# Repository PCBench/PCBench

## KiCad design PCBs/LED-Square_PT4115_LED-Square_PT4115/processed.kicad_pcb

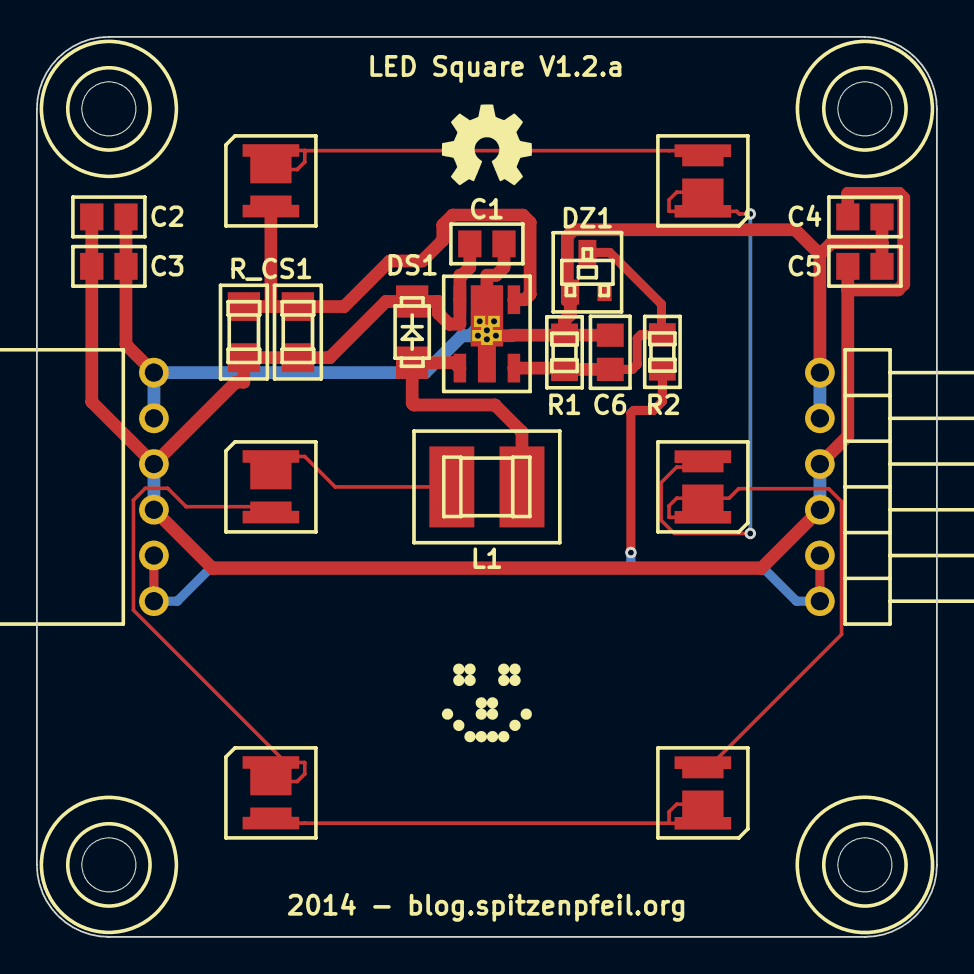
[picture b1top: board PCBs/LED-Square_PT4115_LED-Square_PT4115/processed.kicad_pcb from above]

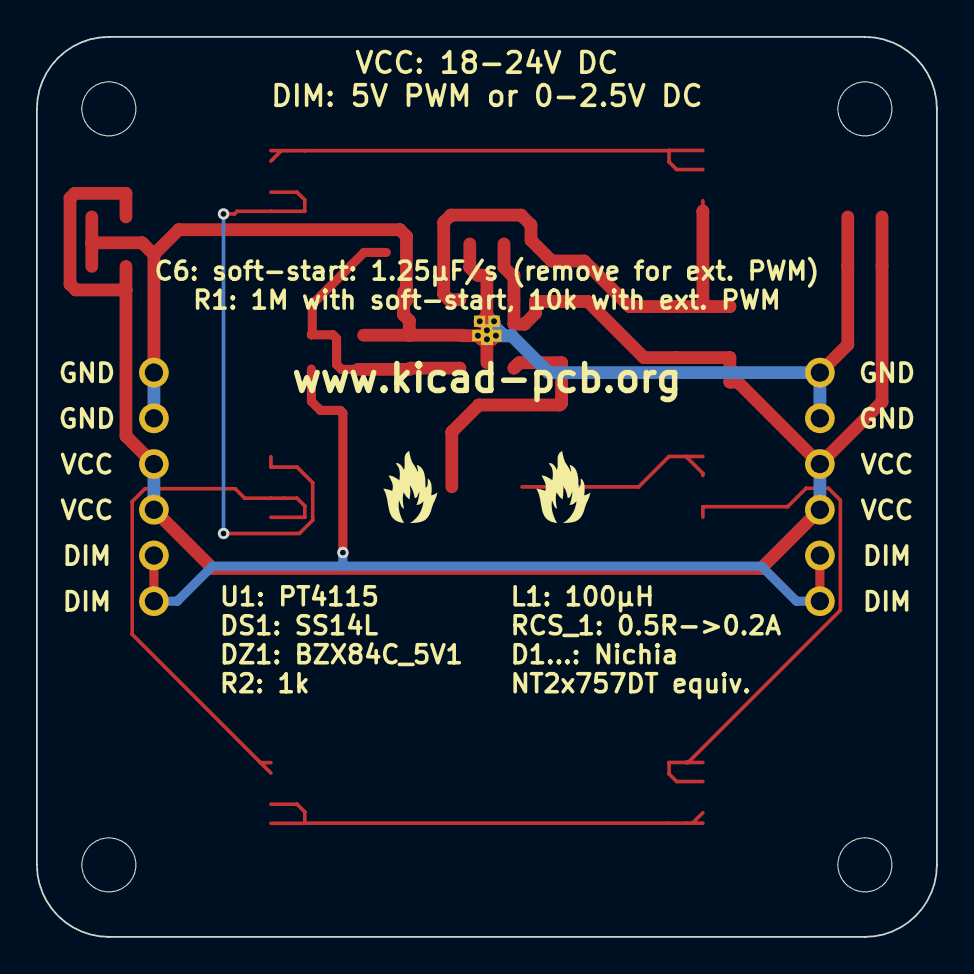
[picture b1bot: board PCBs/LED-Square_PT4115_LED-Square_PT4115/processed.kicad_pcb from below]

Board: 2 copper layers, 50.0 x 50.0 mm, 30 parts (2 on the bottom side), 12 nets.

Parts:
C1, C2, C3, C4, C5: 10µF; MADW__C0805
C6: 1.25µF/s; MADW__C0805
D1, D2, D3, D4, D5, D6: LED; MADW__Nichia-NT2x757DT
DS1: SS14L (40V, 1A); MADW__diode_sub-SMA
DZ1: BZX84C_5V1; MADW__SOT23
G1: OSHW-logo_silkscreen_5mm
G2: LED_smile_silkscreen_5mm
G3, G4: fire_silkscreen-back_4mm
L1: 100µH; MADW__L4.8x3.3mm
MH1, MH2, MH3, MH4: CONN_1; MADW__mounting_hole_3mm
P1: IN; MADW__edge-connector_SIL6_female
P2: OUT; MADW__edge-connector_SIL6_male
R1: 1M; MADW__R0805
R2: 1k; MADW__R0805
R_CS1, R_CS2: 1R1; MADW__R1206
U1: PT4115-SOT89-5; MADW__SOT89-5

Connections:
/CSN: D1.1, R_CS1.2, R_CS2.2, U1.4
/D1HS: D1.2, D2.1
/D2HS: D2.2, D3.1
/D3HS: D3.2, D4.1
/D4HS: D4.2, D5.1
/D5HS: D5.2, D6.1
/D6HS: D6.2, L1.2
/DIM: P1.5, P1.6, P2.1, P2.2, R2.1
/SW: DS1.1, L1.1, U1.1
/_dim: C6.1, DZ1.3, R1.1, R2.2, U1.3
GND: C1.2, C2.2, C3.2, C4.2, C5.2, C6.2, DZ1.1, P1.1, P1.2, P2.5, P2.6, R1.2, U1.2
VCC: C1.1, C2.1, C3.1, C4.1, C5.1, DS1.2, P1.3, P1.4, P2.3, P2.4, R_CS1.1, R_CS2.1, U1.5

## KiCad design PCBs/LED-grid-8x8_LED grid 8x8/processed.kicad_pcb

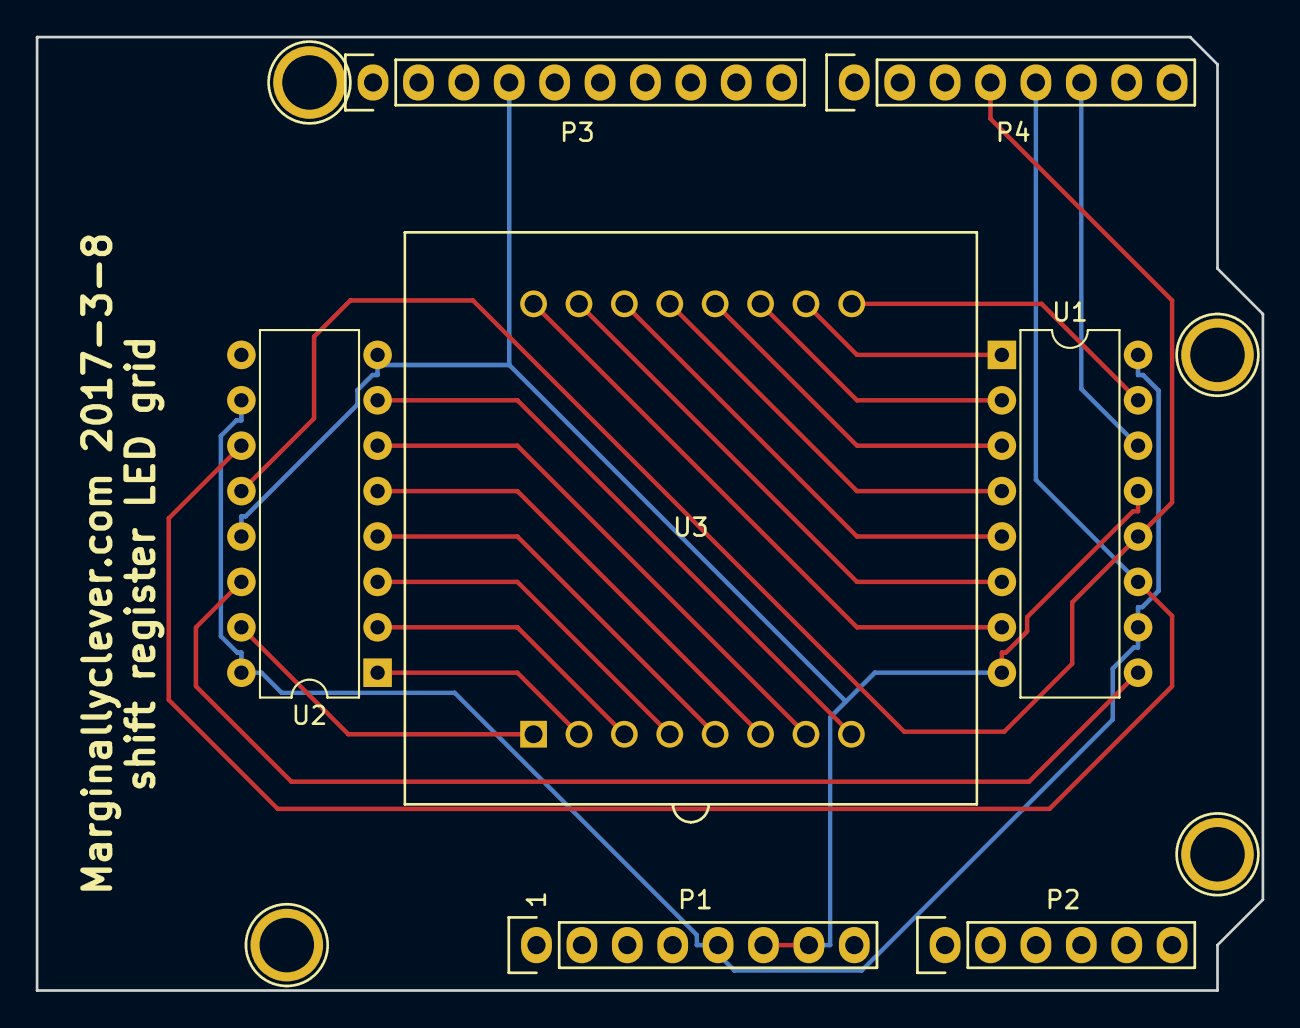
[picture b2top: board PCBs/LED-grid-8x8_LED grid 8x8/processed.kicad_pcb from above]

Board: 2 copper layers, 68.6 x 53.3 mm, 11 parts (0 on the bottom side), 22 nets.

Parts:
P1: Power; Socket_Strip_Arduino_1x08
P2: Analog; Socket_Strip_Arduino_1x06
P3: Digital; Socket_Strip_Arduino_1x10
P4: Digital; Socket_Strip_Arduino_1x08
P5, P6, P7, P8: CONN_1; Arduino_1pin
U1, U2: 74HC595; DIP-16_W7.62mm
U3: 1088BS

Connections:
+5V: P1.5, U1.10, U1.16, U2.10, U2.16
/2: P4.6, U1.14
/3(**): P4.5, U1.11, U2.11
/4: P4.4, U1.12, U2.12
GND: P1.6, P1.7, P3.4, U1.8, U1.13, U2.8, U2.13
unnamed: U1.1, U3.10
unnamed: U1.2, U3.11
unnamed: U1.3, U3.12
unnamed: U1.4, U3.13
unnamed: U1.5, U3.14
unnamed: U1.6, U3.15
unnamed: U1.7, U3.16
unnamed: U1.9, U2.14
unnamed: U1.15, U3.9
unnamed: U2.1, U3.2
unnamed: U2.2, U3.3
unnamed: U2.3, U3.4
unnamed: U2.4, U3.5
unnamed: U2.5, U3.6
unnamed: U2.6, U3.7
unnamed: U2.7, U3.8
unnamed: U2.15, U3.1

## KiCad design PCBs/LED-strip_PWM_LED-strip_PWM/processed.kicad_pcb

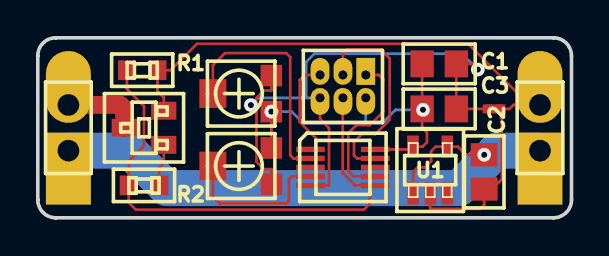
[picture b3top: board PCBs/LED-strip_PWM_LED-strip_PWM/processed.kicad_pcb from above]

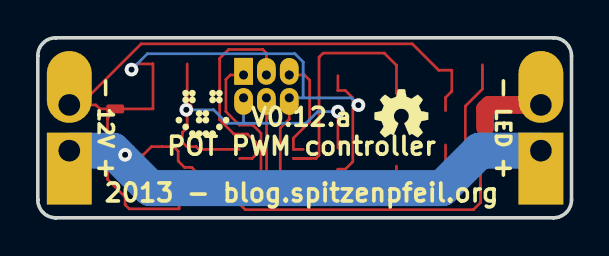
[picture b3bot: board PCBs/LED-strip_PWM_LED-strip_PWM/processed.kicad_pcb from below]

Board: 2 copper layers, 29.7 x 10.0 mm, 16 parts (2 on the bottom side), 12 nets.

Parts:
C1, C2: 100nF; MADW__C0805
C3: 4.7µF; MADW__C0805
G1: OSHW-logo_silkscreen_3mm
G2: LED_smile_silkscreen_3mm
IC1: MADW__ATTINY13-MM; MADW__MLF10
JP1: ISP; MADW__PIN_ARRAY_3x2_1.27mm
NJ1: NET-JOIN; MADW__SMD-net-noin-0.5mm
P1, P2: CONN_2; MADW__SIL-2
R1: 100k; MADW__R0603_2
R2: 150R; MADW__R0603_2
RV1, RV2: 50k; MADW__TC33X-POT
T1: AO3400; MADW__SOT23
U1: MCP1804-SOT23-5; MADW__SOT23-5

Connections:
/MISO: IC1.7, JP1.1
/MOSI: IC1.6, JP1.4, R1.2, R2.1
/POT1: IC1.2, RV1.2
/POT2: IC1.4, RV2.2
/RESET: IC1.1, JP1.5
/SCK: IC1.9, JP1.3
/Vin: C2.1, P1.1, P2.1, U1.1, U1.4
/drain: P2.2, T1.3
GND: C1.2, C3.2, IC1.5, JP1.6, NJ1.1, RV1.3, RV2.1
GNDPWR: C2.2, NJ1.2, P1.2, R1.1, T1.2, U1.2
unnamed: R2.2, T1.1
VCC: C1.1, C3.1, IC1.10, JP1.2, RV1.1, RV2.3, U1.5

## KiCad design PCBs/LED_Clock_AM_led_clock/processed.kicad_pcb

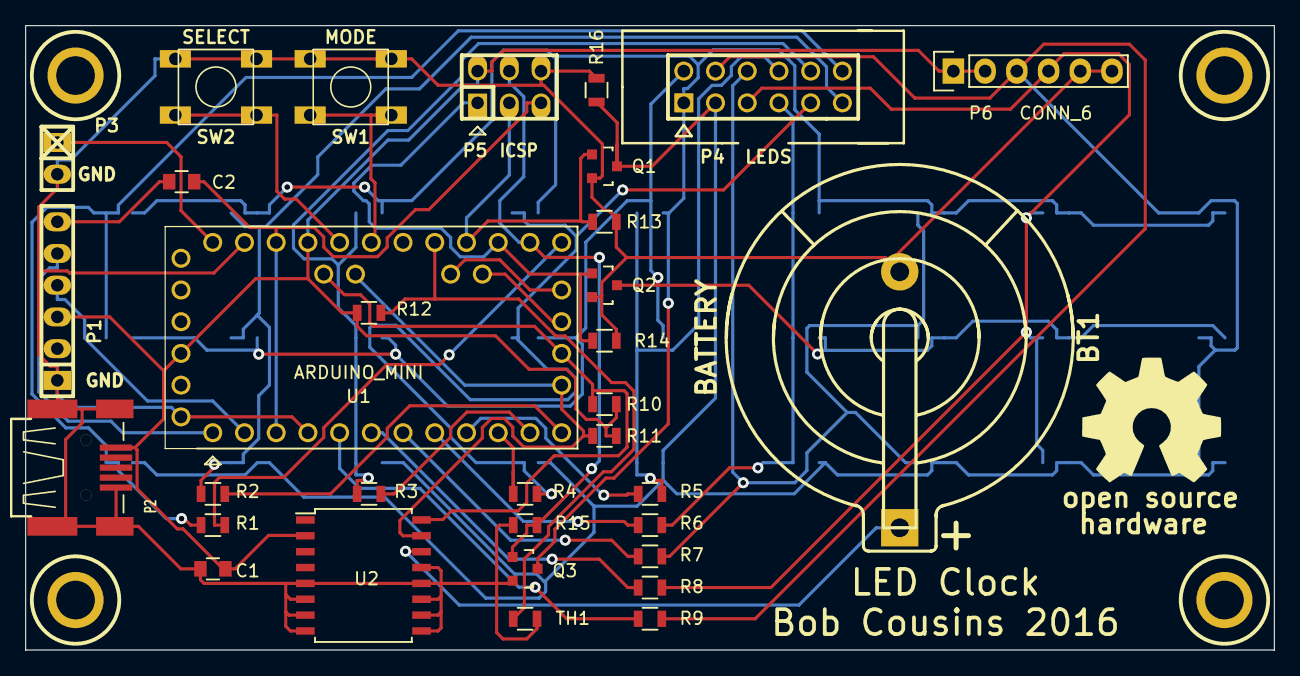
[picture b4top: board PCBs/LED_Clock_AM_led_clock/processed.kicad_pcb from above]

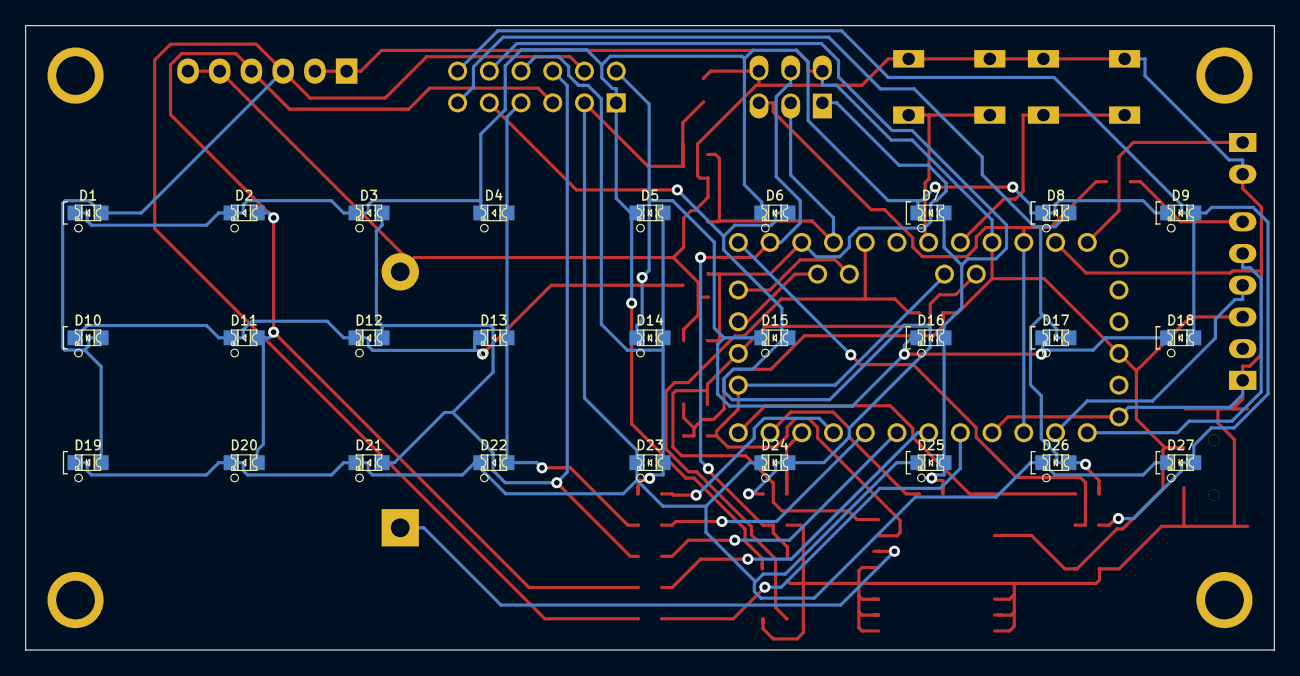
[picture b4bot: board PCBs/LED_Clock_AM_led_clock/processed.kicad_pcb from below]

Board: 2 copper layers, 100.0 x 50.0 mm, 65 parts (27 on the bottom side), 37 nets.

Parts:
BT1: BATTERY; keystone_106
C1, C2: 100nF; C_0805
D1, D7, D8, D9, D10, D16, D17, D18, D19, D25, D26, D27: LED; LED-0805_RED
D2, D3, D4, D11, D12, D13, D20, D21, D22: LED; LED-0805_GREEN
D5, D6, D14, D15, D23, D24: LED; LED-0805_BLUE
H1, H2, H3, H4: HOLE_RMC; HOLE_M3
M2: LOGO_OSHW; OSHW_logo_2
P1: SERIAL; pin_strip_6
P2: USBCONN; CONN_MiniAB_SMT_RMC
P3: 5-9V IN; pin_strip_2
P4: LEDS; PIN_ARRAY_6x2_RMC
P5: ICSP; pin_strip_3x2
P6: CONN_6; Pin_Header_Straight_1x06
Q1, Q2, Q3: BSS138; SOT-23
R1, R2, R3, R4, R5, R6, R7, R8, R9: 220; R_0805
R10, R11, R12: 4k7; R_0805
R13, R14, R15: 10k; R_0805
R16: 0R; R_0805
SW1: MODE; SW_6x6_MULTI
SW2: SELECT; SW_6x6_MULTI
TH1: 10k; R_0805
U1: ARDUINO_MINI
U2: DS3231N; SOIC-16_7.5x10.3mm_Pitch1.27mm

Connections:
+5V: C1.1, P1.3, P2.1, P5.2, P6.1, P6.2, R10.2, R11.2, R12.1, U1.+5V, U2.2
/MISO: P5.1, Q2.1, R14.1, U1.12
/MOSI: P5.4, Q3.1, R15.1, U1.11
/SCK: P5.3, Q1.1, R13.1, U1.13
/SCL: R10.1, U1.A5, U2.16
/SDA: R11.1, U1.A4, U2.15
/SW1: SW1.1, U1.A2
/SW2: SW2.1, U1.A3
/VIN: P3.1, U1.VIN
/~RST: C2.2, P5.5, U1.RST
COL1: D1.2, D10.2, D19.2, P4.4, P6.3, R9.2
COL2: D2.2, D11.2, D20.2, P4.5, P6.4, R8.2
COL3: D3.2, D12.2, D21.2, P4.6, R7.2
COL4: D4.2, D13.2, D22.2, P4.7, R6.2
COL5: D5.2, D14.2, D23.2, P4.8, R5.2
COL6: D6.2, D15.2, D24.2, P4.9, R4.2
COL7: D7.2, D16.2, D25.2, P4.10, R3.2
COL8: D8.2, D17.2, D26.2, P4.11, R2.2
COL9: D9.2, D18.2, D27.2, P4.12, R1.2
GND: BT1.2, C1.2, P1.1, P2.4, P2.5, P3.2, P5.6, P6.5, P6.6, Q1.2, Q2.2, Q3.2, R13.2, R14.2, R15.2, R16.2, SW1.2, SW2.2, TH1.2, U1.GND, U2.5, U2.6, U2.7, U2.8, U2.9, U2.10, U2.11, U2.12, U2.13
unnamed: BT1.1, U2.14
unnamed: C2.1, P1.6
unnamed: R1.1, U1.10
unnamed: R2.1, U1.9
unnamed: R3.1, U1.8
unnamed: R4.1, U1.7
unnamed: R5.1, U1.6
unnamed: R6.1, U1.5
unnamed: R7.1, U1.4
unnamed: R8.1, U1.3
unnamed: R9.1, U1.2
unnamed: R12.2, TH1.1, U1.A0
ROW1: D1.1, D2.1, D3.1, D4.1, D5.1, D6.1, D7.1, D8.1, D9.1, P4.1, Q3.3
ROW2: D10.1, D11.1, D12.1, D13.1, D14.1, D15.1, D16.1, D17.1, D18.1, P4.2, Q2.3
ROW3: D19.1, D20.1, D21.1, D22.1, D23.1, D24.1, D25.1, D26.1, D27.1, P4.3, Q1.3, R16.1
RX: P1.4, U1.0
TX: P1.5, U1.1

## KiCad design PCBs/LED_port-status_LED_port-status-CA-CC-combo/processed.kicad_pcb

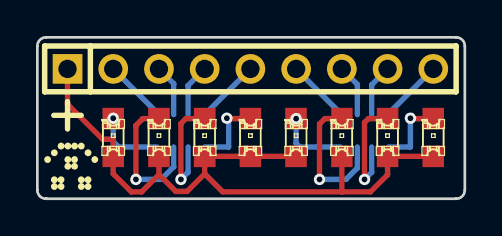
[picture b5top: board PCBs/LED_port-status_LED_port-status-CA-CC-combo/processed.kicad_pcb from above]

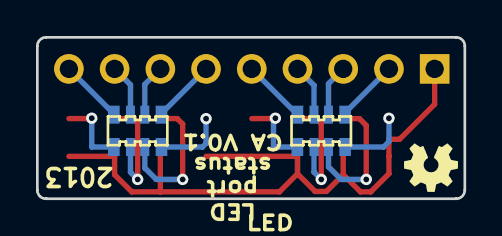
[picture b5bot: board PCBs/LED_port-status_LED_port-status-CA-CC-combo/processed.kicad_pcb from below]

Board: 2 copper layers, 23.7 x 9.0 mm, 15 parts (4 on the bottom side), 17 nets.

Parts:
D1, D2, D3, D4, D5, D6, D7, D8: LED; LED-0805
G1, G1_2: LED_smile_silkscreen_3mm
G2, G2_2: OSHW-logo_silkscreen_3mm
P1: CONN_9; SIL-9
RP1, RP2: 1k; MADW__1206*4_resistor_array

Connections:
unnamed: P1.9, RP1.4
unnamed: P1.8, RP1.3
unnamed: P1.7, RP1.2
unnamed: P1.6, RP1.1
unnamed: P1.5, RP2.4
unnamed: P1.4, RP2.3
unnamed: P1.3, RP2.2
unnamed: P1.2, RP2.1
unnamed: D1.2, RP1.5
unnamed: D6.2, RP2.6
unnamed: D8.2, RP2.8
unnamed: D5.2, RP2.5
unnamed: D4.2, RP1.8
unnamed: D2.2, RP1.6
unnamed: D7.2, RP2.7
unnamed: D3.2, RP1.7
unnamed: D1.1, D2.1, D3.1, D4.1, D5.1, D6.1, D7.1, D8.1, P1.1
